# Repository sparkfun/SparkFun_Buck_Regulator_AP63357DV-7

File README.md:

SparkFun 5V Buck Regulator Breakouts - AP63357
========================================

<p align="center">

</p>

These buck regulator boards feature the AP63357 from [Diodes Inc.](https://www.diodes.com/), a 3.5A synchronous buck converter with a wide input voltage range of 3.8V to 32V. The fully integrated 74m&ohm; high-side power MOSFET/40m low-side power MOSFET provide a high-efficiency step-down DC/DC conversion. The boards are configured to provide a regulated **5V** output and feature a high-voltage `EN` *(enable)* control pin that is rated up to 32V. The boards also include 0.1" spaced PTH pins to connect the input and output power and a copper pad is provided to attach a heat sink to the bottom of the board; to dissipate excess heat.

| [5V Buck Regulator (COM-21255)](https://www.sparkfun.com/products/21255) | [5V BabyBuck Regulator (COM-21256)](https://www.sparkfun.com/products/21256) |
| --- | --- |
|  |  |
| The [Buck regulator breakout board](https://www.sparkfun.com/products/21255), has additional options for connecting input and output power. There is a pre-assembled screw terminal for a non-permanent connection and the option to solder on a [barrel jack](https://www.sparkfun.com/products/119) for an [external power supply](https://www.sparkfun.com/categories/308). The board also includes and red, power indication LED for when the power output is enabled. | Unlike its sibling, the [BabyBuck](https://www.sparkfun.com/products/21256) is a minimalistic board that sacrifices the connection options for space. Don't worry, though, because the PTH pins are still available to connect the input and output power. All of this snuggled up in a low-profile, .63" x .52" board. |

Repository Contents
-------------------

* **[/docs](/docs/)** - Online documentation files
    * [board_files](/docs/board_files/) - Files for the product design
        * [Eagle design files](/docs/board_files/eagle_files.zip) (.zip)
        * [Schematic](/docs/board_files/schematic.pdf) (.pdf)
        * [Dimensions](/docs/board_files/dimensions.pdf) (.pdf)
    * [component_documentation](/docs/component_documentation/) - Datasheets for hardware components
    * [img/hookup_guide/](/docs/img/hookup_guide/) - Images for hookup guide documentation
* **[/Hardware](/Hardware/)** - Eagle design files (.brd, .sch)

Documentation
--------------
* **[Hookup Guide (mkdocs)](http://docs.sparkfun.com/SparkFun_Buck_Regulator_AP63357DV-7/)** - Hookup Guide for the 5V Buck Regulator Breakouts

Product Variants
----------------
* **AP63357 - 5V Buck Regulators**
    * COM-21255: [SparkFun Buck Regulator Breakout - 5V (AP63357DV)](https://www.sparkfun.com/products/21255)
    * COM-21256: [SparkFun BabyBuck Regulator Breakout - 5V (AP63357DV)](https://www.sparkfun.com/products/21256)
* **AP63203 - 3.3V Buck Regulators**
    * COM-18356: [SparkFun Buck Regulator Breakout - 3.3V (AP63203)](https://www.sparkfun.com/products/18356)
    * COM-18357: [SparkFun BabyBuck Regulator Breakout - 3.3V (AP63203)](https://www.sparkfun.com/products/18357)
* **AP3429A - 3.3V & 1.8V Buck Regulators**
    * COM-21337: [SparkFun Buck Regulator Breakout - 3.3V (AP63203)](https://www.sparkfun.com/products/21337)
    * COM-21338: [SparkFun Buck Regulator Breakout - 1.8V (AP63203)](https://www.sparkfun.com/products/21338)

Version History
---------------
* [v01](https://github.com/sparkfun/SparkFun_Buck_Regulator_AP63357DV-7/releases/tag/v01) - Initial Release

License Information
-------------------

This product is _**open source**_! 

Please review the LICENSE.md file for license information. 

If you have any questions or concerns about licensing, please contact technical support on our [SparkFun forums](https://forum.sparkfun.com/viewforum.php?f=152).

Distributed as-is; no warranty is given.

- Your friends at SparkFun.

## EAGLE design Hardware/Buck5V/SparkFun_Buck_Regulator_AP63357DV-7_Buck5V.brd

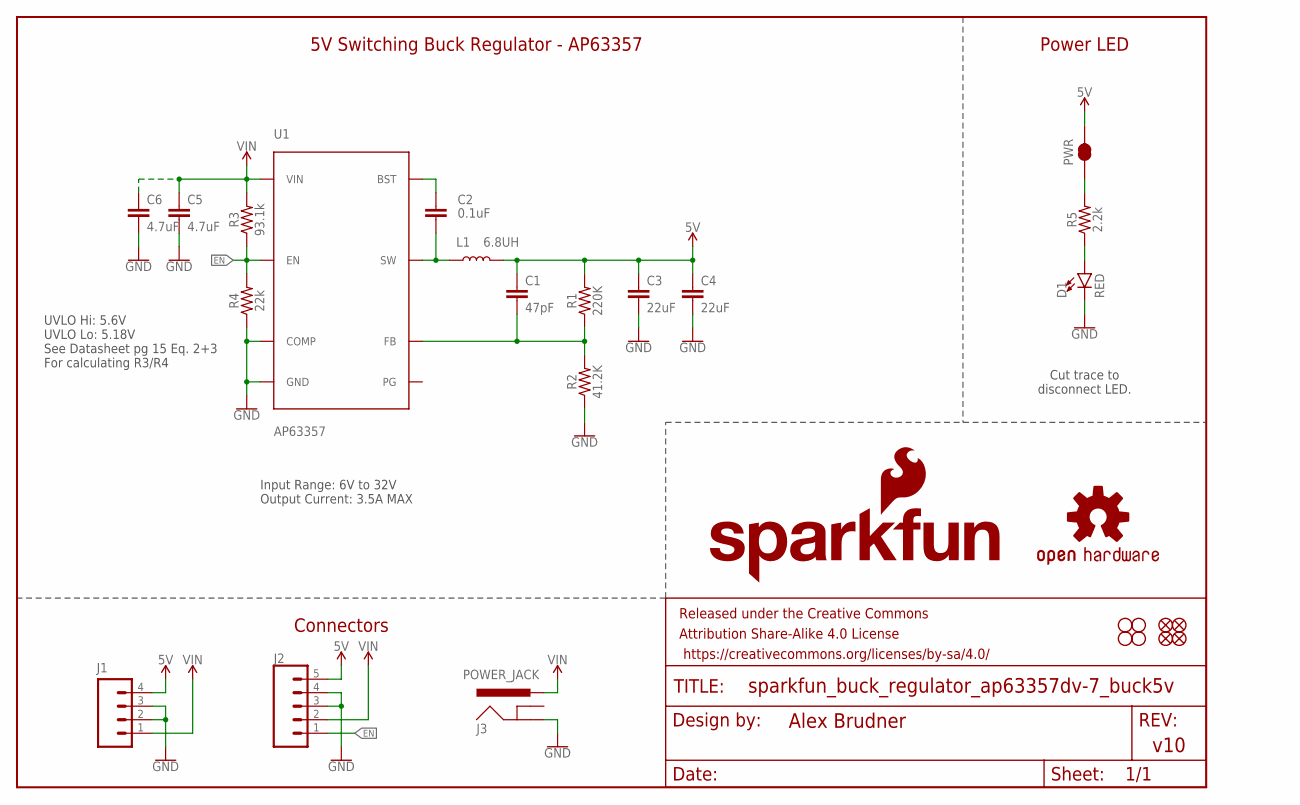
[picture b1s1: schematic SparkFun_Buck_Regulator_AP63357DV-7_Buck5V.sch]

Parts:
C1: 47pF; 0402-TIGHT
C2: 0.1uF; 0402-TIGHT
C3, C4: 22uF; 0805
C5, C6: 4.7uF; 0805
D1: RED; LED-0603
FD1, FD2, FD3, FD4: FIDUCIALUFIDUCIAL; FIDUCIAL-MICRO
FRAME1: FRAME-LEDGER; CREATIVE_COMMONS
H1, H2, H3, H4: STAND-OFF
J1: CONN_04SCREW; SCREWTERMINAL-3.5MM-4
J2: CONN_05NO_SILK; 1X05_NO_SILK
J3: POWER_JACK; POWER_JACK_PTH_SLOT_NO_OVRHNG_SILK
L1: 6.8UH; 07A7_6U8H
LOGO1: OSHW-LOGOMINI; OSHW-LOGO-MINI
LOGO2: SFE_LOGO_NAME_FLAME.1_INCH; SFE_LOGO_NAME_FLAME_.1
PWR: JUMPER-SMT_2_NC_TRACE_SILK; SMT-JUMPER_2_NC_TRACE_SILK
R1: 220K; 0402-TIGHT
R2: 41.2K; 0402-TIGHT
R3: 93.1k; 0402-TIGHT
R4: 22k; 0402-TIGHT
R5: 2.2k; 0402-TIGHT
U1: AP63357; V-DFN3020-13

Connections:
5V: C1.1, C3.1, C4.1, J1.4, J2.5, L1.P$2 (2), PWR.2, R1.2
EN: J2.1, R3.1, R4.2, U1.P$2 (EN)
FB: C1.2, R1.1, R2.2, U1.P$3 (FB)
GND: C3.2, C4.2, C5.2, C6.2, D1.C, J1.2, J1.3, J2.3, J2.4, J3.GND, R2.1, R4.1, U1.P$4 (COMP), U1.P$8 (GND)
unnamed: D1.A, R5.1
unnamed: C2.1, U1.P$6 (BST)
unnamed: PWR.1, R5.2
SW: C2.2, L1.P$1 (1), U1.P$7 (SW), U1.P$9 (SW)
VIN: C5.1, C6.1, J1.1, J2.2, J3.PWR, R3.2, U1.P$1 (VIN)

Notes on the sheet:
Power LED
Connectors
5V Switching Buck Regulator - AP63357
Input Range: 6V to 32V Output Current: 3.5A MAX
Cut trace to disconnect LED.
UVLO Hi: 5.6V UVLO Lo: 5.18V See Datasheet pg 15 Eq. 2+3 For calculating R3/R4

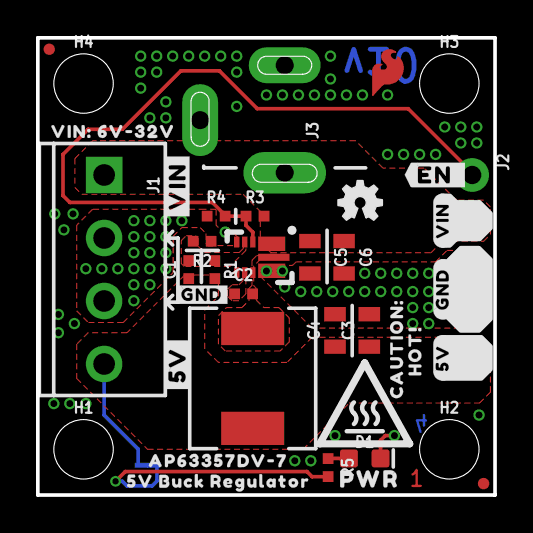
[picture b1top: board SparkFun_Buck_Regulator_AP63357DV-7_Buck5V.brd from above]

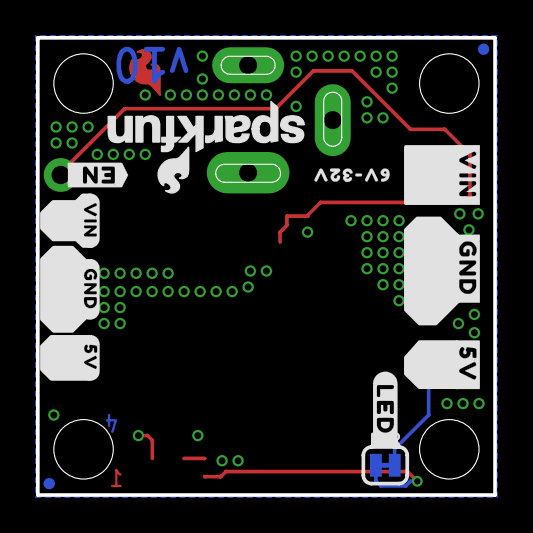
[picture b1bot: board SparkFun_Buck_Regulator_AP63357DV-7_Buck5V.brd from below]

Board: 4 copper layers, 25.4 x 25.4 mm, 54 parts (13 on the bottom side), 9 nets.

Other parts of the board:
U$1: AP63357DV#70
U$2: 5V_BUCK_REGULATOR0
U$3: #5V#4
U$4: #VIN#8
U$5, U$13: #VIN#0
U$6, U$7: #GND#0
U$8, U$19: #EN_#0
U$9: #GND#9
U$10: #5V#10
U$11: 6V#32V10
U$12: HOT##0
U$14, U$24: #5V#0
U$15: #LED_#0
U$16: CAUTION#0
U$17: SFE_LOGO_FLAME_COPPER_EXPOSED_.1
U$18: VIN#_6V#32V0
U$20: PWR0
U$21: #GND#1
U$22: HIGH_TEMP_WARNING
U$23: ORDERING_INSTRUCTIONS
U$26: #VIN#3

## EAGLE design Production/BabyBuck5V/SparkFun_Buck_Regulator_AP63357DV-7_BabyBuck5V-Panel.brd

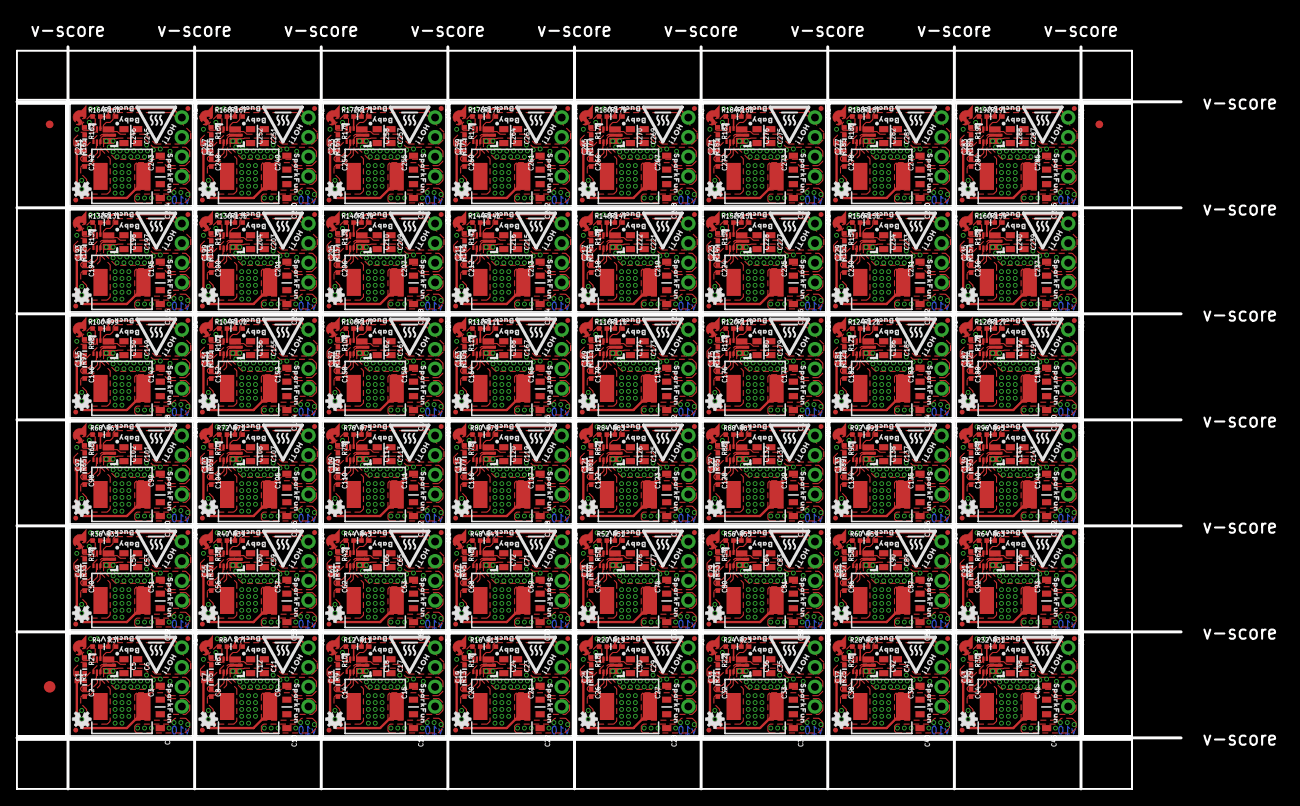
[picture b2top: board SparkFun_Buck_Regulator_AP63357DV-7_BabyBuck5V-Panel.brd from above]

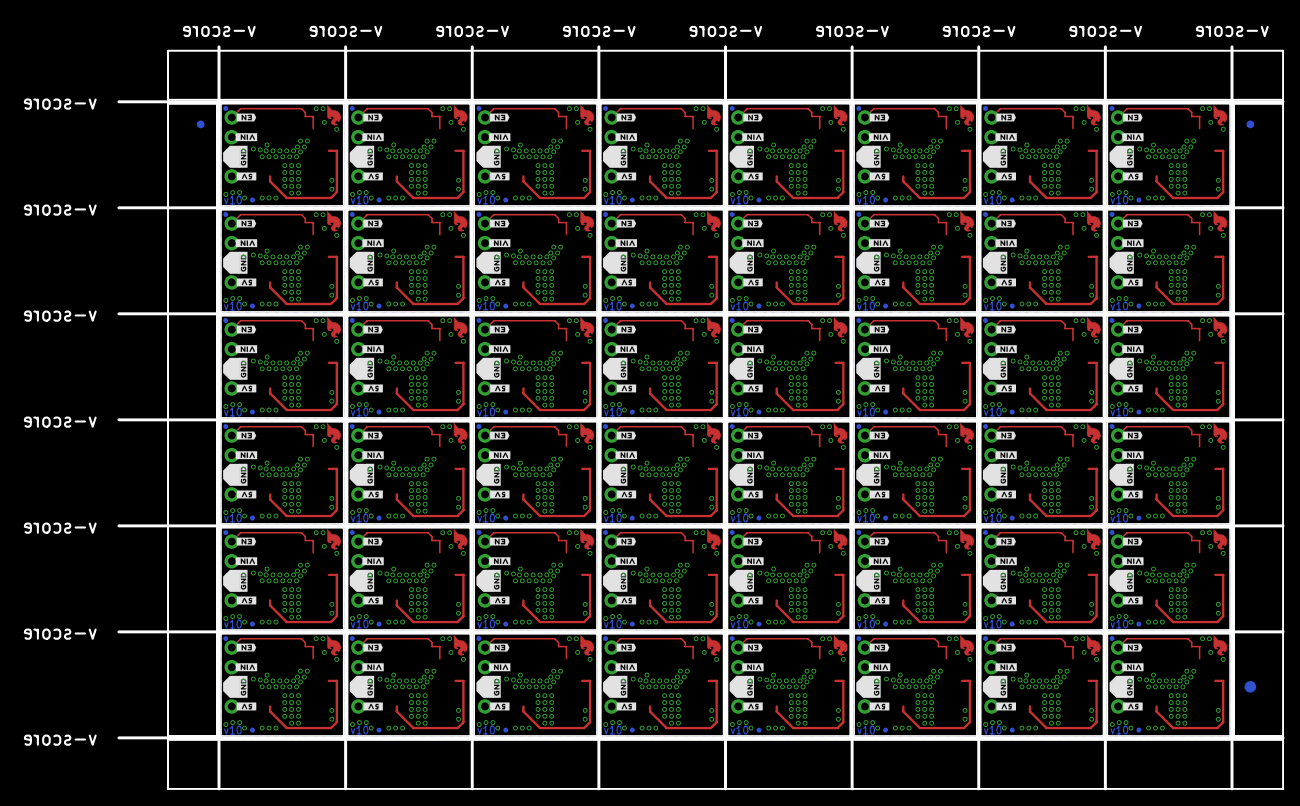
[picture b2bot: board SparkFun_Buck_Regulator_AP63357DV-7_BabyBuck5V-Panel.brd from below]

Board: 4 copper layers, 150.6 x 96.0 mm, 1446 parts (291 on the bottom side), 336 nets.

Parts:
C1, C7, C13, C19, C25, C31, C37, C43, C49, C55, C61, C67, C73, C79, C85, C91, C97, C103, C109, C115, C121, C127, C133, C139, C145, C151, C157, C163, C169, C175, C181, C187, C193, C199, C205, C211, C217, C223, C229, C235, C241, C247, C253, C259, C265, C271, C277, C283: 47pF; 0402-TIGHT
C2, C8, C14, C20, C26, C32, C38, C44, C50, C56, C62, C68, C74, C80, C86, C92, C98, C104, C110, C116, C122, C128, C134, C140, C146, C152, C158, C164, C170, C176, C182, C188, C194, C200, C206, C212, C218, C224, C230, C236, C242, C248, C254, C260, C266, C272, C278, C284: 0.1uF; 0402-TIGHT
C3, C4, C9, C10, C15, C16, C21, C22, C27, C28, C33, C34, C39, C40, C45, C46, C51, C52, C57, C58, C63, C64, C69, C70, C75, C76, C81, C82, C87, C88, C93, C94, C99, C100, C105, C106, C111, C112, C117, C118, C123, C124, C129, C130, C135, C136, C141, C142, C147, C148, C153, C154, C159, C160, C165, C166, C171, C172, C177, C178, C183, C184, C189, C190, C195, C196, C201, C202, C207, C208, C213, C214, C219, C220, C225, C226, C231, C232, C237, C238, C243, C244, C249, C250, C255, C256, C261, C262, C267, C268, C273, C274, C279, C280, C285, C286: 22uF; 0805
C5, C6, C11, C12, C17, C18, C23, C24, C29, C30, C35, C36, C41, C42, C47, C48, C53, C54, C59, C60, C65, C66, C71, C72, C77, C78, C83, C84, C89, C90, C95, C96, C101, C102, C107, C108, C113, C114, C119, C120, C125, C126, C131, C132, C137, C138, C143, C144, C149, C150, C155, C156, C161, C162, C167, C168, C173, C174, C179, C180, C185, C186, C191, C192, C197, C198, C203, C204, C209, C210, C215, C216, C221, C222, C227, C228, C233, C234, C239, C240, C245, C246, C251, C252, C257, C258, C263, C264, C269, C270, C275, C276, C281, C282, C287, C288: 4.7uF; 0805
E$1, E$2, E$3, E$4: FIDUCIAL-1X2
E$5, E$6: FIDUCIAL-1.5X3
FD1, FD2, FD3, FD4, FD5, FD6, FD7, FD8, FD9, FD10, FD11, FD12, FD13, FD14, FD15, FD16, FD17, FD18, FD19, FD20, FD21, FD22, FD23, FD24, FD25, FD26, FD27, FD28, FD29, FD30, FD31, FD32, FD33, FD34, FD35, FD36, FD37, FD38, FD39, FD40, FD41, FD42, FD43, FD44, FD45, FD46, FD47, FD48, FD49, FD50, FD51, FD52, FD53, FD54, FD55, FD56, FD57, FD58, FD59, FD60, FD61, FD62, FD63, FD64, FD65, FD66, FD67, FD68, FD69, FD70, FD71, FD72, FD73, FD74, FD75, FD76, FD77, FD78, FD79, FD80, FD81, FD82, FD83, FD84, FD85, FD86, FD87, FD88, FD89, FD90, FD91, FD92, FD93, FD94, FD95, FD96, FD97, FD98, FD99, FD100, FD101, FD102, FD103, FD104, FD105, FD106, FD107, FD108, FD109, FD110, FD111, FD112, FD113, FD114, FD115, FD116, FD117, FD118, FD119, FD120, FD121, FD122, FD123, FD124, FD125, FD126, FD127, FD128, FD129, FD130, FD131, FD132, FD133, FD134, FD135, FD136, FD137, FD138, FD139, FD140, FD141, FD142, FD143, FD144, FD145, FD146, FD147, FD148, FD149, FD150, FD151, FD152, FD153, FD154, FD155, FD156, FD157, FD158, FD159, FD160, FD161, FD162, FD163, FD164, FD165, FD166, FD167, FD168, FD169, FD170, FD171, FD172, FD173, FD174, FD175, FD176, FD177, FD178, FD179, FD180, FD181, FD182, FD183, FD184, FD185, FD186, FD187, FD188, FD189, FD190, FD191, FD192: FIDUCIALUFIDUCIAL; FIDUCIAL-MICRO
J1, J2, J3, J4, J5, J6, J7, J8, J9, J10, J11, J12, J13, J14, J15, J16, J17, J18, J19, J20, J21, J22, J23, J24, J25, J26, J27, J28, J29, J30, J31, J32, J33, J34, J35, J36, J37, J38, J39, J40, J41, J42, J43, J44, J45, J46, J47, J48: 1X04_NO_SILK
L1, L2, L3, L4, L5, L6, L7, L8, L9, L10, L11, L12, L13, L14, L15, L16, L17, L18, L19, L20, L21, L22, L23, L24, L25, L26, L27, L28, L29, L30, L31, L32, L33, L34, L35, L36, L37, L38, L39, L40, L41, L42, L43, L44, L45, L46, L47, L48: 6.8UH; 07A7_6U8H
LOGO1, LOGO4, LOGO6, LOGO8, LOGO10, LOGO12, LOGO14, LOGO16, LOGO18, LOGO20, LOGO22, LOGO24, LOGO26, LOGO28, LOGO30, LOGO32, LOGO34, LOGO36, LOGO38, LOGO40, LOGO42, LOGO44, LOGO46, LOGO48, LOGO50, LOGO52, LOGO54, LOGO56, LOGO58, LOGO60, LOGO62, LOGO64, LOGO66, LOGO68, LOGO70, LOGO72, LOGO74, LOGO76, LOGO78, LOGO80, LOGO82, LOGO84, LOGO86, LOGO88, LOGO90, LOGO92, LOGO94, LOGO96: SFE_LOGO_NAME_FLAMEBLANK; BLANK
LOGO2, LOGO3, LOGO5, LOGO7, LOGO9, LOGO11, LOGO13, LOGO15, LOGO17, LOGO19, LOGO21, LOGO23, LOGO25, LOGO27, LOGO29, LOGO31, LOGO33, LOGO35, LOGO37, LOGO39, LOGO41, LOGO43, LOGO45, LOGO47, LOGO49, LOGO51, LOGO53, LOGO55, LOGO57, LOGO59, LOGO61, LOGO63, LOGO65, LOGO67, LOGO69, LOGO71, LOGO73, LOGO75, LOGO77, LOGO79, LOGO81, LOGO83, LOGO85, LOGO87, LOGO89, LOGO91, LOGO93, LOGO95: OSHW-LOGOMINI; OSHW-LOGO-MINI
R1, R5, R9, R13, R17, R21, R25, R29, R33, R37, R41, R45, R49, R53, R57, R61, R65, R69, R73, R77, R81, R85, R89, R93, R97, R101, R105, R109, R113, R117, R121, R125, R129, R133, R137, R141, R145, R149, R153, R157, R161, R165, R169, R173, R177, R181, R185, R189: 220K; 0402-TIGHT
R2, R6, R10, R14, R18, R22, R26, R30, R34, R38, R42, R46, R50, R54, R58, R62, R66, R70, R74, R78, R82, R86, R90, R94, R98, R102, R106, R110, R114, R118, R122, R126, R130, R134, R138, R142, R146, R150, R154, R158, R162, R166, R170, R174, R178, R182, R186, R190: 41.2K; 0402-TIGHT
R3, R7, R11, R15, R19, R23, R27, R31, R35, R39, R43, R47, R51, R55, R59, R63, R67, R71, R75, R79, R83, R87, R91, R95, R99, R103, R107, R111, R115, R119, R123, R127, R131, R135, R139, R143, R147, R151, R155, R159, R163, R167, R171, R175, R179, R183, R187, R191: 93.1k; 0402-TIGHT
R4, R8, R12, R16, R20, R24, R28, R32, R36, R40, R44, R48, R52, R56, R60, R64, R68, R72, R76, R80, R84, R88, R92, R96, R100, R104, R108, R112, R116, R120, R124, R128, R132, R136, R140, R144, R148, R152, R156, R160, R164, R168, R172, R176, R180, R184, R188, R192: 22k; 0402-TIGHT
U1, U2, U3, U4, U5, U6, U7, U8, U9, U10, U11, U12, U13, U14, U15, U16, U17, U18, U19, U20, U21, U22, U23, U24, U25, U26, U27, U28, U29, U30, U31, U32, U33, U34, U35, U36, U37, U38, U39, U40, U41, U42, U43, U44, U45, U46, U47, U48: AP63357; V-DFN3020-13
U$1, U$11, U$23, U$34, U$45, U$56, U$67, U$78, U$89, U$100, U$111, U$122, U$133, U$144, U$155, U$166, U$177, U$188, U$199, U$210, U$221, U$232, U$243, U$254, U$265, U$276, U$287, U$298, U$309, U$320, U$331, U$342, U$353, U$364, U$375, U$386, U$397, U$408, U$419, U$430, U$441, U$452, U$463, U$474, U$485, U$496, U$507, U$518: SFE_LOGO_FLAME_COPPER_EXPOSED_.1
U$2, U$18, U$29, U$40, U$51, U$62, U$73, U$84, U$95, U$106, U$117, U$128, U$139, U$150, U$161, U$172, U$183, U$194, U$205, U$216, U$227, U$238, U$249, U$260, U$271, U$282, U$293, U$304, U$315, U$326, U$337, U$348, U$359, U$370, U$381, U$392, U$403, U$414, U$425, U$436, U$447, U$458, U$469, U$480, U$491, U$502, U$513, U$524: #EN_#10
U$3, U$19, U$30, U$41, U$52, U$63, U$74, U$85, U$96, U$107, U$118, U$129, U$140, U$151, U$162, U$173, U$184, U$195, U$206, U$217, U$228, U$239, U$250, U$261, U$272, U$283, U$294, U$305, U$316, U$327, U$338, U$349, U$360, U$371, U$382, U$393, U$404, U$415, U$426, U$437, U$448, U$459, U$470, U$481, U$492, U$503, U$514, U$525: #VIN_#11
U$4, U$20, U$31, U$42, U$53, U$64, U$75, U$86, U$97, U$108, U$119, U$130, U$141, U$152, U$163, U$174, U$185, U$196, U$207, U$218, U$229, U$240, U$251, U$262, U$273, U$284, U$295, U$306, U$317, U$328, U$339, U$350, U$361, U$372, U$383, U$394, U$405, U$416, U$427, U$438, U$449, U$460, U$471, U$482, U$493, U$504, U$515, U$526: #GND#13
U$5, U$21, U$32, U$43, U$54, U$65, U$76, U$87, U$98, U$109, U$120, U$131, U$142, U$153, U$164, U$175, U$186, U$197, U$208, U$219, U$230, U$241, U$252, U$263, U$274, U$285, U$296, U$307, U$318, U$329, U$340, U$351, U$362, U$373, U$384, U$395, U$406, U$417, U$428, U$439, U$450, U$461, U$472, U$483, U$494, U$505, U$516, U$527: #_5V_#6
U$6, U$13, U$25, U$36, U$47, U$58, U$69, U$80, U$91, U$102, U$113, U$124, U$135, U$146, U$157, U$168, U$179, U$190, U$201, U$212, U$223, U$234, U$245, U$256, U$267, U$278, U$289, U$300, U$311, U$322, U$333, U$344, U$355, U$366, U$377, U$388, U$399, U$410, U$421, U$432, U$443, U$454, U$465, U$476, U$487, U$498, U$509, U$520: BABY0
U$7, U$15, U$26, U$37, U$48, U$59, U$70, U$81, U$92, U$103, U$114, U$125, U$136, U$147, U$158, U$169, U$180, U$191, U$202, U$213, U$224, U$235, U$246, U$257, U$268, U$279, U$290, U$301, U$312, U$323, U$334, U$345, U$356, U$367, U$378, U$389, U$400, U$411, U$422, U$433, U$444, U$455, U$466, U$477, U$488, U$499, U$510, U$521: BUCK0
U$8, U$12, U$24, U$35, U$46, U$57, U$68, U$79, U$90, U$101, U$112, U$123, U$134, U$145, U$156, U$167, U$178, U$189, U$200, U$211, U$222, U$233, U$244, U$255, U$266, U$277, U$288, U$299, U$310, U$321, U$332, U$343, U$354, U$365, U$376, U$387, U$398, U$409, U$420, U$431, U$442, U$453, U$464, U$475, U$486, U$497, U$508, U$519: HIGH_TEMP_WARNING
U$9, U$16, U$27, U$38, U$49, U$60, U$71, U$82, U$93, U$104, U$115, U$126, U$137, U$148, U$159, U$170, U$181, U$192, U$203, U$214, U$225, U$236, U$247, U$258, U$269, U$280, U$291, U$302, U$313, U$324, U$335, U$346, U$357, U$368, U$379, U$390, U$401, U$412, U$423, U$434, U$445, U$456, U$467, U$478, U$489, U$500, U$511, U$522: 5V0
U$10, U$22, U$33, U$44, U$55, U$66, U$77, U$88, U$99, U$110, U$121, U$132, U$143, U$154, U$165, U$176, U$187, U$198, U$209, U$220, U$231, U$242, U$253, U$264, U$275, U$286, U$297, U$308, U$319, U$330, U$341, U$352, U$363, U$374, U$385, U$396, U$407, U$418, U$429, U$440, U$451, U$462, U$473, U$484, U$495, U$506, U$517, U$528: HOT##7
U$14, U$17, U$28, U$39, U$50, U$61, U$72, U$83, U$94, U$105, U$116, U$127, U$138, U$149, U$160, U$171, U$182, U$193, U$204, U$215, U$226, U$237, U$248, U$259, U$270, U$281, U$292, U$303, U$314, U$325, U$336, U$347, U$358, U$369, U$380, U$391, U$402, U$413, U$424, U$435, U$446, U$457, U$468, U$479, U$490, U$501, U$512, U$523: SPARKFUN0

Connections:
5V: C1.1, C3.1, C4.1, J1.4, L1.P$2, R1.2
5V1: C7.1, C9.1, C10.1, J2.4, L2.P$2, R5.2
5V2: C13.1, C15.1, C16.1, J3.4, L3.P$2, R9.2
5V3: C19.1, C21.1, C22.1, J4.4, L4.P$2, R13.2
5V4: C25.1, C27.1, C28.1, J5.4, L5.P$2, R17.2
5V5: C31.1, C33.1, C34.1, J6.4, L6.P$2, R21.2
5V6: C37.1, C39.1, C40.1, J7.4, L7.P$2, R25.2
5V7: C43.1, C45.1, C46.1, J8.4, L8.P$2, R29.2
5V8: C49.1, C51.1, C52.1, J9.4, L9.P$2, R33.2
5V9: C55.1, C57.1, C58.1, J10.4, L10.P$2, R37.2
5V10: C61.1, C63.1, C64.1, J11.4, L11.P$2, R41.2
5V11: C67.1, C69.1, C70.1, J12.4, L12.P$2, R45.2
5V12: C73.1, C75.1, C76.1, J13.4, L13.P$2, R49.2
5V13: C79.1, C81.1, C82.1, J14.4, L14.P$2, R53.2
5V14: C85.1, C87.1, C88.1, J15.4, L15.P$2, R57.2
5V15: C91.1, C93.1, C94.1, J16.4, L16.P$2, R61.2
5V16: C97.1, C99.1, C100.1, J17.4, L17.P$2, R65.2
5V17: C103.1, C105.1, C106.1, J18.4, L18.P$2, R69.2
5V18: C109.1, C111.1, C112.1, J19.4, L19.P$2, R73.2
5V19: C115.1, C117.1, C118.1, J20.4, L20.P$2, R77.2
5V20: C121.1, C123.1, C124.1, J21.4, L21.P$2, R81.2
5V21: C127.1, C129.1, C130.1, J22.4, L22.P$2, R85.2
5V22: C133.1, C135.1, C136.1, J23.4, L23.P$2, R89.2
5V23: C139.1, C141.1, C142.1, J24.4, L24.P$2, R93.2
5V24: C145.1, C147.1, C148.1, J25.4, L25.P$2, R97.2
5V25: C151.1, C153.1, C154.1, J26.4, L26.P$2, R101.2
5V26: C157.1, C159.1, C160.1, J27.4, L27.P$2, R105.2
5V27: C163.1, C165.1, C166.1, J28.4, L28.P$2, R109.2
5V28: C169.1, C171.1, C172.1, J29.4, L29.P$2, R113.2
5V29: C175.1, C177.1, C178.1, J30.4, L30.P$2, R117.2
5V30: C181.1, C183.1, C184.1, J31.4, L31.P$2, R121.2
5V31: C187.1, C189.1, C190.1, J32.4, L32.P$2, R125.2
5V32: C193.1, C195.1, C196.1, J33.4, L33.P$2, R129.2
5V33: C199.1, C201.1, C202.1, J34.4, L34.P$2, R133.2
5V34: C205.1, C207.1, C208.1, J35.4, L35.P$2, R137.2
5V35: C211.1, C213.1, C214.1, J36.4, L36.P$2, R141.2
5V36: C217.1, C219.1, C220.1, J37.4, L37.P$2, R145.2
5V37: C223.1, C225.1, C226.1, J38.4, L38.P$2, R149.2
5V38: C229.1, C231.1, C232.1, J39.4, L39.P$2, R153.2
5V39: C235.1, C237.1, C238.1, J40.4, L40.P$2, R157.2
5V40: C241.1, C243.1, C244.1, J41.4, L41.P$2, R161.2
5V41: C247.1, C249.1, C250.1, J42.4, L42.P$2, R165.2
5V42: C253.1, C255.1, C256.1, J43.4, L43.P$2, R169.2
5V43: C259.1, C261.1, C262.1, J44.4, L44.P$2, R173.2
5V44: C265.1, C267.1, C268.1, J45.4, L45.P$2, R177.2
5V45: C271.1, C273.1, C274.1, J46.4, L46.P$2, R181.2
5V46: C277.1, C279.1, C280.1, J47.4, L47.P$2, R185.2
5V47: C283.1, C285.1, C286.1, J48.4, L48.P$2, R189.2
EN: J1.1, R3.1, R4.2, U1.P$2
EN1: J2.1, R7.1, R8.2, U2.P$2
EN2: J3.1, R11.1, R12.2, U3.P$2
EN3: J4.1, R15.1, R16.2, U4.P$2
EN4: J5.1, R19.1, R20.2, U5.P$2
EN5: J6.1, R23.1, R24.2, U6.P$2
EN6: J7.1, R27.1, R28.2, U7.P$2
EN7: J8.1, R31.1, R32.2, U8.P$2
EN8: J9.1, R35.1, R36.2, U9.P$2
EN9: J10.1, R39.1, R40.2, U10.P$2
EN10: J11.1, R43.1, R44.2, U11.P$2
EN11: J12.1, R47.1, R48.2, U12.P$2
EN12: J13.1, R51.1, R52.2, U13.P$2
EN13: J14.1, R55.1, R56.2, U14.P$2
EN14: J15.1, R59.1, R60.2, U15.P$2
EN15: J16.1, R63.1, R64.2, U16.P$2
EN16: J17.1, R67.1, R68.2, U17.P$2
EN17: J18.1, R71.1, R72.2, U18.P$2
EN18: J19.1, R75.1, R76.2, U19.P$2
EN19: J20.1, R79.1, R80.2, U20.P$2
EN20: J21.1, R83.1, R84.2, U21.P$2
EN21: J22.1, R87.1, R88.2, U22.P$2
EN22: J23.1, R91.1, R92.2, U23.P$2
EN23: J24.1, R95.1, R96.2, U24.P$2
EN24: J25.1, R99.1, R100.2, U25.P$2
EN25: J26.1, R103.1, R104.2, U26.P$2
EN26: J27.1, R107.1, R108.2, U27.P$2
EN27: J28.1, R111.1, R112.2, U28.P$2
EN28: J29.1, R115.1, R116.2, U29.P$2
EN29: J30.1, R119.1, R120.2, U30.P$2
EN30: J31.1, R123.1, R124.2, U31.P$2
EN31: J32.1, R127.1, R128.2, U32.P$2
EN32: J33.1, R131.1, R132.2, U33.P$2
EN33: J34.1, R135.1, R136.2, U34.P$2
EN34: J35.1, R139.1, R140.2, U35.P$2
EN35: J36.1, R143.1, R144.2, U36.P$2
EN36: J37.1, R147.1, R148.2, U37.P$2
EN37: J38.1, R151.1, R152.2, U38.P$2
EN38: J39.1, R155.1, R156.2, U39.P$2
EN39: J40.1, R159.1, R160.2, U40.P$2
EN40: J41.1, R163.1, R164.2, U41.P$2
EN41: J42.1, R167.1, R168.2, U42.P$2
EN42: J43.1, R171.1, R172.2, U43.P$2
EN43: J44.1, R175.1, R176.2, U44.P$2
EN44: J45.1, R179.1, R180.2, U45.P$2
EN45: J46.1, R183.1, R184.2, U46.P$2
EN46: J47.1, R187.1, R188.2, U47.P$2
EN47: J48.1, R191.1, R192.2, U48.P$2
FB: C1.2, R1.1, R2.2, U1.P$3
FB1: C7.2, R5.1, R6.2, U2.P$3
FB2: C13.2, R9.1, R10.2, U3.P$3
FB3: C19.2, R13.1, R14.2, U4.P$3
FB4: C25.2, R17.1, R18.2, U5.P$3
FB5: C31.2, R21.1, R22.2, U6.P$3
FB6: C37.2, R25.1, R26.2, U7.P$3
FB7: C43.2, R29.1, R30.2, U8.P$3
FB8: C49.2, R33.1, R34.2, U9.P$3
FB9: C55.2, R37.1, R38.2, U10.P$3
FB10: C61.2, R41.1, R42.2, U11.P$3
FB11: C67.2, R45.1, R46.2, U12.P$3
FB12: C73.2, R49.1, R50.2, U13.P$3
FB13: C79.2, R53.1, R54.2, U14.P$3
FB14: C85.2, R57.1, R58.2, U15.P$3
FB15: C91.2, R61.1, R62.2, U16.P$3
FB16: C97.2, R65.1, R66.2, U17.P$3
FB17: C103.2, R69.1, R70.2, U18.P$3
FB18: C109.2, R73.1, R74.2, U19.P$3
FB19: C115.2, R77.1, R78.2, U20.P$3
FB20: C121.2, R81.1, R82.2, U21.P$3
FB21: C127.2, R85.1, R86.2, U22.P$3
FB22: C133.2, R89.1, R90.2, U23.P$3
FB23: C139.2, R93.1, R94.2, U24.P$3
FB24: C145.2, R97.1, R98.2, U25.P$3
FB25: C151.2, R101.1, R102.2, U26.P$3
FB26: C157.2, R105.1, R106.2, U27.P$3
FB27: C163.2, R109.1, R110.2, U28.P$3
FB28: C169.2, R113.1, R114.2, U29.P$3
FB29: C175.2, R117.1, R118.2, U30.P$3
FB30: C181.2, R121.1, R122.2, U31.P$3
FB31: C187.2, R125.1, R126.2, U32.P$3
FB32: C193.2, R129.1, R130.2, U33.P$3
FB33: C199.2, R133.1, R134.2, U34.P$3
FB34: C205.2, R137.1, R138.2, U35.P$3
FB35: C211.2, R141.1, R142.2, U36.P$3
FB36: C217.2, R145.1, R146.2, U37.P$3
FB37: C223.2, R149.1, R150.2, U38.P$3
FB38: C229.2, R153.1, R154.2, U39.P$3
FB39: C235.2, R157.1, R158.2, U40.P$3
FB40: C241.2, R161.1, R162.2, U41.P$3
FB41: C247.2, R165.1, R166.2, U42.P$3
FB42: C253.2, R169.1, R170.2, U43.P$3
FB43: C259.2, R173.1, R174.2, U44.P$3
FB44: C265.2, R177.1, R178.2, U45.P$3
FB45: C271.2, R181.1, R182.2, U46.P$3
FB46: C277.2, R185.1, R186.2, U47.P$3
FB47: C283.2, R189.1, R190.2, U48.P$3
GND: C3.2, C4.2, C5.2, C6.2, J1.3, R2.1, R4.1, U1.P$4, U1.P$8
GND1: C9.2, C10.2, C11.2, C12.2, J2.3, R6.1, R8.1, U2.P$4, U2.P$8
GND2: C15.2, C16.2, C17.2, C18.2, J3.3, R10.1, R12.1, U3.P$4, U3.P$8
GND3: C21.2, C22.2, C23.2, C24.2, J4.3, R14.1, R16.1, U4.P$4, U4.P$8
GND4: C27.2, C28.2, C29.2, C30.2, J5.3, R18.1, R20.1, U5.P$4, U5.P$8
GND5: C33.2, C34.2, C35.2, C36.2, J6.3, R22.1, R24.1, U6.P$4, U6.P$8
GND6: C39.2, C40.2, C41.2, C42.2, J7.3, R26.1, R28.1, U7.P$4, U7.P$8
GND7: C45.2, C46.2, C47.2, C48.2, J8.3, R30.1, R32.1, U8.P$4, U8.P$8
GND8: C51.2, C52.2, C53.2, C54.2, J9.3, R34.1, R36.1, U9.P$4, U9.P$8
GND9: C57.2, C58.2, C59.2, C60.2, J10.3, R38.1, R40.1, U10.P$4, U10.P$8
GND10: C63.2, C64.2, C65.2, C66.2, J11.3, R42.1, R44.1, U11.P$4, U11.P$8
GND11: C69.2, C70.2, C71.2, C72.2, J12.3, R46.1, R48.1, U12.P$4, U12.P$8
GND12: C75.2, C76.2, C77.2, C78.2, J13.3, R50.1, R52.1, U13.P$4, U13.P$8
GND13: C81.2, C82.2, C83.2, C84.2, J14.3, R54.1, R56.1, U14.P$4, U14.P$8
GND14: C87.2, C88.2, C89.2, C90.2, J15.3, R58.1, R60.1, U15.P$4, U15.P$8
GND15: C93.2, C94.2, C95.2, C96.2, J16.3, R62.1, R64.1, U16.P$4, U16.P$8
GND16: C99.2, C100.2, C101.2, C102.2, J17.3, R66.1, R68.1, U17.P$4, U17.P$8
GND17: C105.2, C106.2, C107.2, C108.2, J18.3, R70.1, R72.1, U18.P$4, U18.P$8
GND18: C111.2, C112.2, C113.2, C114.2, J19.3, R74.1, R76.1, U19.P$4, U19.P$8
GND19: C117.2, C118.2, C119.2, C120.2, J20.3, R78.1, R80.1, U20.P$4, U20.P$8
GND20: C123.2, C124.2, C125.2, C126.2, J21.3, R82.1, R84.1, U21.P$4, U21.P$8
GND21: C129.2, C130.2, C131.2, C132.2, J22.3, R86.1, R88.1, U22.P$4, U22.P$8
GND22: C135.2, C136.2, C137.2, C138.2, J23.3, R90.1, R92.1, U23.P$4, U23.P$8
GND23: C141.2, C142.2, C143.2, C144.2, J24.3, R94.1, R96.1, U24.P$4, U24.P$8
GND24: C147.2, C148.2, C149.2, C150.2, J25.3, R98.1, R100.1, U25.P$4, U25.P$8
GND25: C153.2, C154.2, C155.2, C156.2, J26.3, R102.1, R104.1, U26.P$4, U26.P$8
GND26: C159.2, C160.2, C161.2, C162.2, J27.3, R106.1, R108.1, U27.P$4, U27.P$8
GND27: C165.2, C166.2, C167.2, C168.2, J28.3, R110.1, R112.1, U28.P$4, U28.P$8
GND28: C171.2, C172.2, C173.2, C174.2, J29.3, R114.1, R116.1, U29.P$4, U29.P$8
GND29: C177.2, C178.2, C179.2, C180.2, J30.3, R118.1, R120.1, U30.P$4, U30.P$8
GND30: C183.2, C184.2, C185.2, C186.2, J31.3, R122.1, R124.1, U31.P$4, U31.P$8
GND31: C189.2, C190.2, C191.2, C192.2, J32.3, R126.1, R128.1, U32.P$4, U32.P$8
GND32: C195.2, C196.2, C197.2, C198.2, J33.3, R130.1, R132.1, U33.P$4, U33.P$8
GND33: C201.2, C202.2, C203.2, C204.2, J34.3, R134.1, R136.1, U34.P$4, U34.P$8
GND34: C207.2, C208.2, C209.2, C210.2, J35.3, R138.1, R140.1, U35.P$4, U35.P$8
GND35: C213.2, C214.2, C215.2, C216.2, J36.3, R142.1, R144.1, U36.P$4, U36.P$8
GND36: C219.2, C220.2, C221.2, C222.2, J37.3, R146.1, R148.1, U37.P$4, U37.P$8
GND37: C225.2, C226.2, C227.2, C228.2, J38.3, R150.1, R152.1, U38.P$4, U38.P$8
GND38: C231.2, C232.2, C233.2, C234.2, J39.3, R154.1, R156.1, U39.P$4, U39.P$8
GND39: C237.2, C238.2, C239.2, C240.2, J40.3, R158.1, R160.1, U40.P$4, U40.P$8
GND40: C243.2, C244.2, C245.2, C246.2, J41.3, R162.1, R164.1, U41.P$4, U41.P$8
GND41: C249.2, C250.2, C251.2, C252.2, J42.3, R166.1, R168.1, U42.P$4, U42.P$8
GND42: C255.2, C256.2, C257.2, C258.2, J43.3, R170.1, R172.1, U43.P$4, U43.P$8
GND43: C261.2, C262.2, C263.2, C264.2, J44.3, R174.1, R176.1, U44.P$4, U44.P$8
GND44: C267.2, C268.2, C269.2, C270.2, J45.3, R178.1, R180.1, U45.P$4, U45.P$8
GND45: C273.2, C274.2, C275.2, C276.2, J46.3, R182.1, R184.1, U46.P$4, U46.P$8
GND46: C279.2, C280.2, C281.2, C282.2, J47.3, R186.1, R188.1, U47.P$4, U47.P$8
GND47: C285.2, C286.2, C287.2, C288.2, J48.3, R190.1, R192.1, U48.P$4, U48.P$8
unnamed: C8.1, U2.P$6
unnamed: C14.1, U3.P$6
unnamed: C20.1, U4.P$6
unnamed: C2.1, U1.P$6
unnamed: C26.1, U5.P$6
unnamed: C32.1, U6.P$6
unnamed: C38.1, U7.P$6
unnamed: C44.1, U8.P$6
unnamed: C50.1, U9.P$6
unnamed: C56.1, U10.P$6
unnamed: C62.1, U11.P$6
unnamed: C68.1, U12.P$6
unnamed: C74.1, U13.P$6
unnamed: C80.1, U14.P$6
unnamed: C86.1, U15.P$6
unnamed: C92.1, U16.P$6
unnamed: C98.1, U17.P$6
unnamed: C104.1, U18.P$6
unnamed: C110.1, U19.P$6
unnamed: C116.1, U20.P$6
unnamed: C122.1, U21.P$6
unnamed: C128.1, U22.P$6
unnamed: C134.1, U23.P$6
unnamed: C140.1, U24.P$6
unnamed: C146.1, U25.P$6
unnamed: C152.1, U26.P$6
unnamed: C158.1, U27.P$6
unnamed: C164.1, U28.P$6
unnamed: C170.1, U29.P$6
unnamed: C176.1, U30.P$6
unnamed: C182.1, U31.P$6
unnamed: C188.1, U32.P$6
unnamed: C194.1, U33.P$6
unnamed: C200.1, U34.P$6
unnamed: C206.1, U35.P$6
unnamed: C212.1, U36.P$6
unnamed: C218.1, U37.P$6
unnamed: C224.1, U38.P$6
unnamed: C230.1, U39.P$6
unnamed: C236.1, U40.P$6
unnamed: C242.1, U41.P$6
unnamed: C248.1, U42.P$6
unnamed: C254.1, U43.P$6
unnamed: C260.1, U44.P$6
unnamed: C266.1, U45.P$6
unnamed: C272.1, U46.P$6
unnamed: C278.1, U47.P$6
unnamed: C284.1, U48.P$6
SW: C2.2, L1.P$1, U1.P$7, U1.P$9
SW1: C8.2, L2.P$1, U2.P$7, U2.P$9
SW2: C14.2, L3.P$1, U3.P$7, U3.P$9
SW3: C20.2, L4.P$1, U4.P$7, U4.P$9
SW4: C26.2, L5.P$1, U5.P$7, U5.P$9
SW5: C32.2, L6.P$1, U6.P$7, U6.P$9
SW6: C38.2, L7.P$1, U7.P$7, U7.P$9
SW7: C44.2, L8.P$1, U8.P$7, U8.P$9
SW8: C50.2, L9.P$1, U9.P$7, U9.P$9
SW9: C56.2, L10.P$1, U10.P$7, U10.P$9
SW10: C62.2, L11.P$1, U11.P$7, U11.P$9
SW11: C68.2, L12.P$1, U12.P$7, U12.P$9
SW12: C74.2, L13.P$1, U13.P$7, U13.P$9
SW13: C80.2, L14.P$1, U14.P$7, U14.P$9
SW14: C86.2, L15.P$1, U15.P$7, U15.P$9
SW15: C92.2, L16.P$1, U16.P$7, U16.P$9
SW16: C98.2, L17.P$1, U17.P$7, U17.P$9
SW17: C104.2, L18.P$1, U18.P$7, U18.P$9
SW18: C110.2, L19.P$1, U19.P$7, U19.P$9
SW19: C116.2, L20.P$1, U20.P$7, U20.P$9
SW20: C122.2, L21.P$1, U21.P$7, U21.P$9
SW21: C128.2, L22.P$1, U22.P$7, U22.P$9
SW22: C134.2, L23.P$1, U23.P$7, U23.P$9
SW23: C140.2, L24.P$1, U24.P$7, U24.P$9
SW24: C146.2, L25.P$1, U25.P$7, U25.P$9
SW25: C152.2, L26.P$1, U26.P$7, U26.P$9
SW26: C158.2, L27.P$1, U27.P$7, U27.P$9
SW27: C164.2, L28.P$1, U28.P$7, U28.P$9
SW28: C170.2, L29.P$1, U29.P$7, U29.P$9
SW29: C176.2, L30.P$1, U30.P$7, U30.P$9
SW30: C182.2, L31.P$1, U31.P$7, U31.P$9
SW31: C188.2, L32.P$1, U32.P$7, U32.P$9
SW32: C194.2, L33.P$1, U33.P$7, U33.P$9
SW33: C200.2, L34.P$1, U34.P$7, U34.P$9
SW34: C206.2, L35.P$1, U35.P$7, U35.P$9
SW35: C212.2, L36.P$1, U36.P$7, U36.P$9
SW36: C218.2, L37.P$1, U37.P$7, U37.P$9
SW37: C224.2, L38.P$1, U38.P$7, U38.P$9
SW38: C230.2, L39.P$1, U39.P$7, U39.P$9
SW39: C236.2, L40.P$1, U40.P$7, U40.P$9
SW40: C242.2, L41.P$1, U41.P$7, U41.P$9
SW41: C248.2, L42.P$1, U42.P$7, U42.P$9
SW42: C254.2, L43.P$1, U43.P$7, U43.P$9
SW43: C260.2, L44.P$1, U44.P$7, U44.P$9
SW44: C266.2, L45.P$1, U45.P$7, U45.P$9
SW45: C272.2, L46.P$1, U46.P$7, U46.P$9
SW46: C278.2, L47.P$1, U47.P$7, U47.P$9
SW47: C284.2, L48.P$1, U48.P$7, U48.P$9
VIN: C5.1, C6.1, J1.2, R3.2, U1.P$1
VIN1: C11.1, C12.1, J2.2, R7.2, U2.P$1
VIN2: C17.1, C18.1, J3.2, R11.2, U3.P$1
VIN3: C23.1, C24.1, J4.2, R15.2, U4.P$1
VIN4: C29.1, C30.1, J5.2, R19.2, U5.P$1
VIN5: C35.1, C36.1, J6.2, R23.2, U6.P$1
VIN6: C41.1, C42.1, J7.2, R27.2, U7.P$1
VIN7: C47.1, C48.1, J8.2, R31.2, U8.P$1
VIN8: C53.1, C54.1, J9.2, R35.2, U9.P$1
VIN9: C59.1, C60.1, J10.2, R39.2, U10.P$1
VIN10: C65.1, C66.1, J11.2, R43.2, U11.P$1
VIN11: C71.1, C72.1, J12.2, R47.2, U12.P$1
VIN12: C77.1, C78.1, J13.2, R51.2, U13.P$1
VIN13: C83.1, C84.1, J14.2, R55.2, U14.P$1
VIN14: C89.1, C90.1, J15.2, R59.2, U15.P$1
VIN15: C95.1, C96.1, J16.2, R63.2, U16.P$1
VIN16: C101.1, C102.1, J17.2, R67.2, U17.P$1
VIN17: C107.1, C108.1, J18.2, R71.2, U18.P$1
VIN18: C113.1, C114.1, J19.2, R75.2, U19.P$1
VIN19: C119.1, C120.1, J20.2, R79.2, U20.P$1
VIN20: C125.1, C126.1, J21.2, R83.2, U21.P$1
VIN21: C131.1, C132.1, J22.2, R87.2, U22.P$1
VIN22: C137.1, C138.1, J23.2, R91.2, U23.P$1
VIN23: C143.1, C144.1, J24.2, R95.2, U24.P$1
VIN24: C149.1, C150.1, J25.2, R99.2, U25.P$1
VIN25: C155.1, C156.1, J26.2, R103.2, U26.P$1
VIN26: C161.1, C162.1, J27.2, R107.2, U27.P$1
VIN27: C167.1, C168.1, J28.2, R111.2, U28.P$1
VIN28: C173.1, C174.1, J29.2, R115.2, U29.P$1
VIN29: C179.1, C180.1, J30.2, R119.2, U30.P$1
VIN30: C185.1, C186.1, J31.2, R123.2, U31.P$1
VIN31: C191.1, C192.1, J32.2, R127.2, U32.P$1
VIN32: C197.1, C198.1, J33.2, R131.2, U33.P$1
VIN33: C203.1, C204.1, J34.2, R135.2, U34.P$1
VIN34: C209.1, C210.1, J35.2, R139.2, U35.P$1
VIN35: C215.1, C216.1, J36.2, R143.2, U36.P$1
VIN36: C221.1, C222.1, J37.2, R147.2, U37.P$1
VIN37: C227.1, C228.1, J38.2, R151.2, U38.P$1
VIN38: C233.1, C234.1, J39.2, R155.2, U39.P$1
VIN39: C239.1, C240.1, J40.2, R159.2, U40.P$1
VIN40: C245.1, C246.1, J41.2, R163.2, U41.P$1
VIN41: C251.1, C252.1, J42.2, R167.2, U42.P$1
VIN42: C257.1, C258.1, J43.2, R171.2, U43.P$1
VIN43: C263.1, C264.1, J44.2, R175.2, U44.P$1
VIN44: C269.1, C270.1, J45.2, R179.2, U45.P$1
VIN45: C275.1, C276.1, J46.2, R183.2, U46.P$1
VIN46: C281.1, C282.1, J47.2, R187.2, U47.P$1
VIN47: C287.1, C288.1, J48.2, R191.2, U48.P$1

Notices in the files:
README.md:
License: MIT
parts and their libraries:
SparkFun-Aesthetics: Licensing: Creative Commons ShareAlike 4.0 International - https://creativecommons.org/licenses/by-sa/4.0
SparkFun-Aesthetics: Released under the Creative Commons Attribution Share-Alike 4.0 License
SparkFun-Aesthetics: https://creativecommons.org/licenses/by-sa/4.0
